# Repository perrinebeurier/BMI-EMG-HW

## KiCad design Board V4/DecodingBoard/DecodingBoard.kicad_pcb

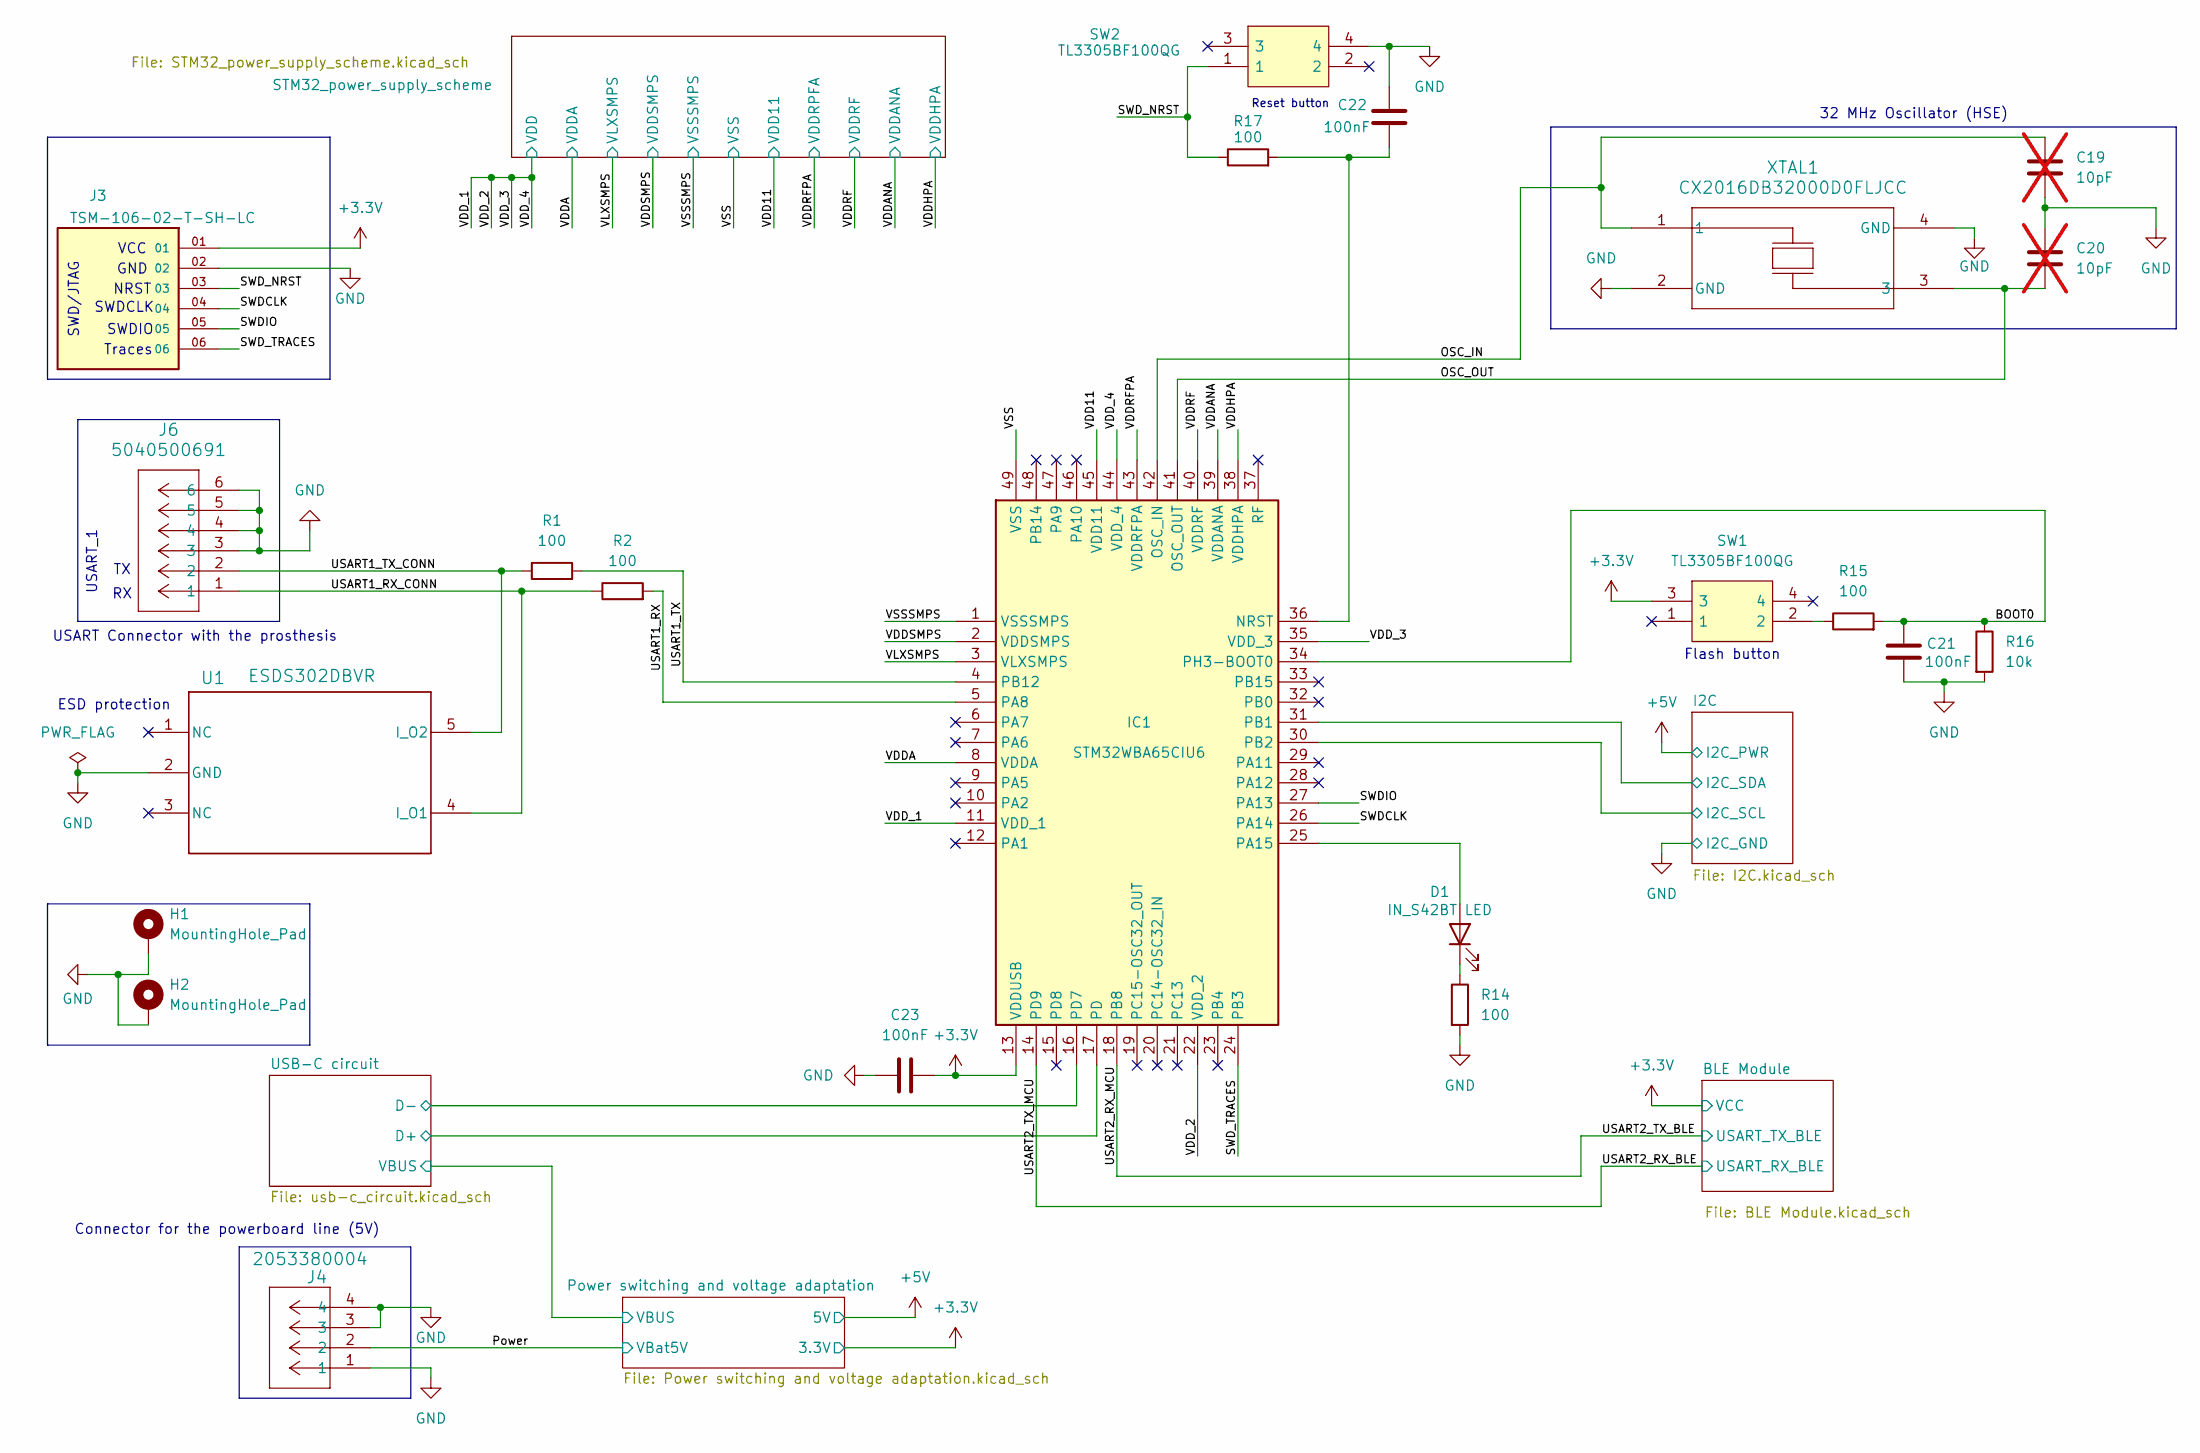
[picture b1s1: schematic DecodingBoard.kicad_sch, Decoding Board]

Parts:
C19, C20: 10pF; C_0603_1608Metric; not fitted
C21, C22, C23: 100nF; C_0402_1005Metric
D1: IN_S42BT LED; LED_0402_1005Metric
H1, H2: MountingHole_Pad; MountingHole_2.2mm_M2_DIN965_Pad
IC1: STM32WBA65CIU6; QFN50P700X700X60-49N-D; Manufacturer_Part_Number STM32WBA65CIU6; Mouser Part Number 511-STM32WBA65CIU6
J3: TSM-106-02-T-SH-LC; SAMTEC_TSM-106-02-T-SH-LC; PARTREV R
J4: 2053380004; CONN_2053380000-SD_02_MOL
J6: 5040500691; CONN_5040500491_MOL
R1, R2, R14, R15, R17: 100; R_0402_1005Metric
R16: 10k; R_0402_1005Metric
SW1, SW2: TL3305BF100QG; TL3305BF160QG; Mouser Part Number 612-TL3305BF100QG
U1: ESDS302DBVR; SOT95P280X145-5N; Mouser Part Number 595-ESDS302DBVR
XTAL1: CX2016DB32000D0FLJCC; Mouser Part Number 581-CX2016DB32DFLJCC

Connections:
+3.3V: C23.2, IC1.2 (VDDSMPS), IC1.8 (VDDA), IC1.11 (VDD_1), IC1.13 (VDDUSB), IC1.22 (VDD_2), IC1.35 (VDD_3), IC1.40 (VDDRF), IC1.44 (VDD_4), J3.01, SW1.3; also elsewhere on the board
/BOOT0: C21.1, IC1.34 (PH3-BOOT0), R15.2, R16.1
/I2C/I2C_SCL: IC1.30 (PB2); also elsewhere on the board
/I2C/I2C_SDA: IC1.31 (PB1); also elsewhere on the board
/OSC_IN: C19.1, IC1.42 (OSC_IN), XTAL1.1
/OSC_OUT: C20.2, IC1.41 (OSC_OUT), XTAL1.3
/Power: J4.2; also elsewhere on the board
/SWDCLK: IC1.26 (PA14), J3.04
/SWDIO: IC1.27 (PA13), J3.05
/SWD_NRST: J3.03, R17.1, SW2.1
/SWD_TRACES: IC1.24 (PB3), J3.06
/USART1_RX: IC1.5 (PA8), R2.2
/USART1_RX_CONN: J6.1, R2.1, U1.4 (I_O1)
/USART1_TX: IC1.4 (PB12), R1.2
/USART1_TX_CONN: J6.2, R1.1, U1.5 (I_O2)
/USART2_RX_BLE: IC1.14 (PD9); also elsewhere on the board
/USART2_RX_MCU: IC1.18 (PB8); also elsewhere on the board
/USB-C circuit/D+: IC1.17 (PD); also elsewhere on the board
/USB-C circuit/D-: IC1.16 (PD7); also elsewhere on the board
/VDD11: IC1.39 (VDDANA), IC1.43 (VDDRFPA), IC1.45 (VDD11); also elsewhere on the board
/VDDHPA: IC1.38 (VDDHPA); also elsewhere on the board
/VLXSMPS: IC1.3 (VLXSMPS); also elsewhere on the board
GND: C19.2, C20.1, C21.2, C22.2, C23.1, H1.1 (1_1), H2.1 (1_1), IC1.1 (VSSSMPS), IC1.49 (VSS), J3.02, J4.1, J4.3, J4.4, J6.3, J6.4, J6.5, J6.6, R14.2, R16.2, SW2.4, U1.2 (GND), XTAL1.2 (GND), XTAL1.4 (GND); also elsewhere on the board
unnamed: D1.2 (A), IC1.25 (PA15)
unnamed: D1.1 (K), R14.1
unnamed: C22.1, IC1.36 (NRST), R17.2
unnamed: R15.1, SW1.2

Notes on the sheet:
GND
SWDIO
Flash button
NRST
ESD protection
Traces
USART Connector with the prosthesis
USART_1
SWD/JTAG
Connector for the powerboard line (5V)
SWDCLK
VCC
Reset button
32 MHz Oscillator (HSE)

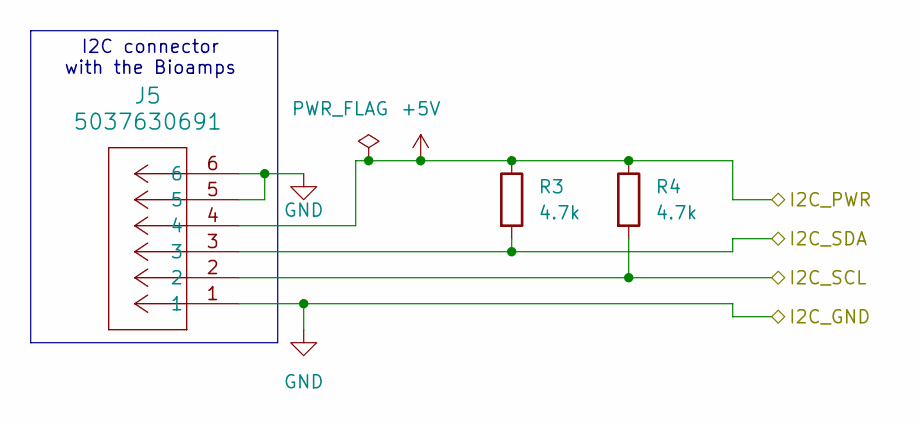
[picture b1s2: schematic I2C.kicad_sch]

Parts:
J5: 5037630691; CONN_5037630000-SD_04_MOL
R3, R4: 4.7k; R_0603_1608Metric

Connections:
+5V: J5.4, R3.1, R4.1; also elsewhere on the board
/I2C/I2C_SCL: J5.2, R4.2; also elsewhere on the board
/I2C/I2C_SDA: J5.3, R3.2; also elsewhere on the board
GND: J5.1, J5.5, J5.6; also elsewhere on the board

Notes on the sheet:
I2C connector with the Bioamps

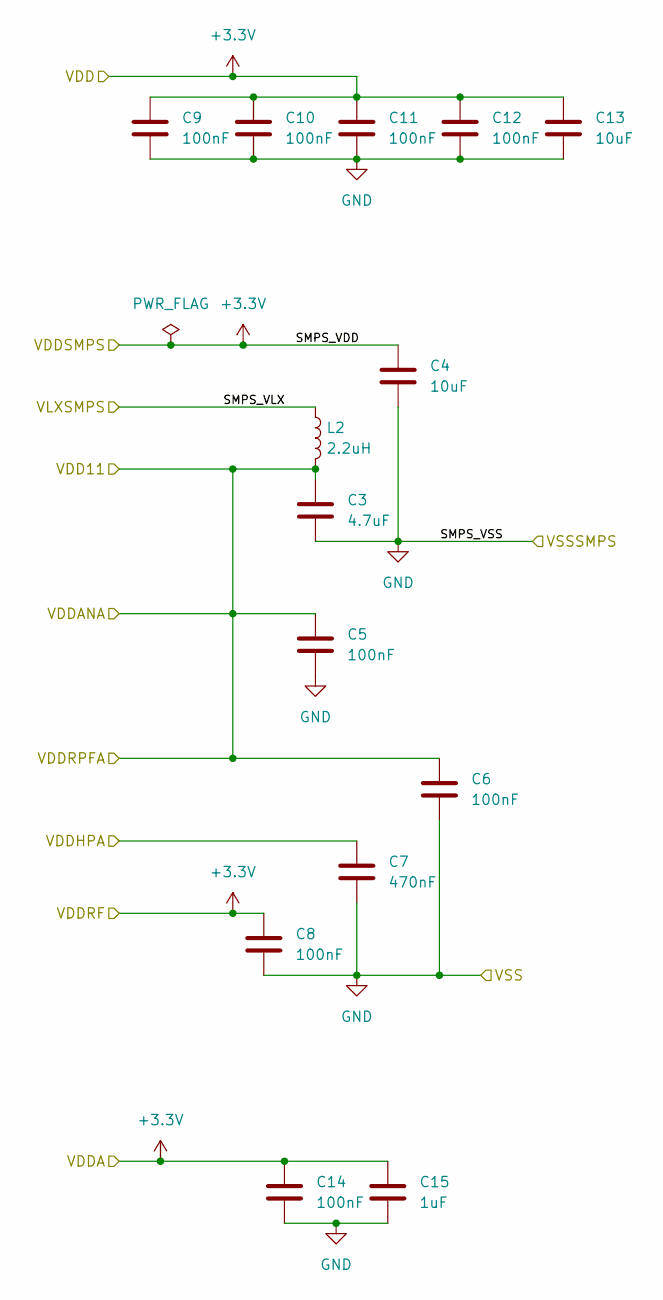
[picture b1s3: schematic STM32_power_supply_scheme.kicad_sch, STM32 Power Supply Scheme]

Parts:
C3: 4.7uF; C_0603_1608Metric
C4, C13: 10uF; C_0603_1608Metric
C5, C6, C8, C9, C10, C11, C12, C14: 100nF; C_0402_1005Metric
C7: 470nF; C_0402_1005Metric
C15: 1uF; C_0402_1005Metric
L2: 2.2uH; L_0805_2012Metric

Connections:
+3.3V: C4.1, C8.1, C9.1, C10.1, C11.1, C12.1, C13.1, C14.1, C15.1; also elsewhere on the board
/VDD11: C3.1, C5.1, C6.1, L2.2; also elsewhere on the board
/VDDHPA: C7.1; also elsewhere on the board
/VLXSMPS: L2.1; also elsewhere on the board
GND: C3.2, C4.2, C5.2, C6.2, C7.2, C8.2, C9.2, C10.2, C11.2, C12.2, C13.2, C14.2, C15.2; also elsewhere on the board

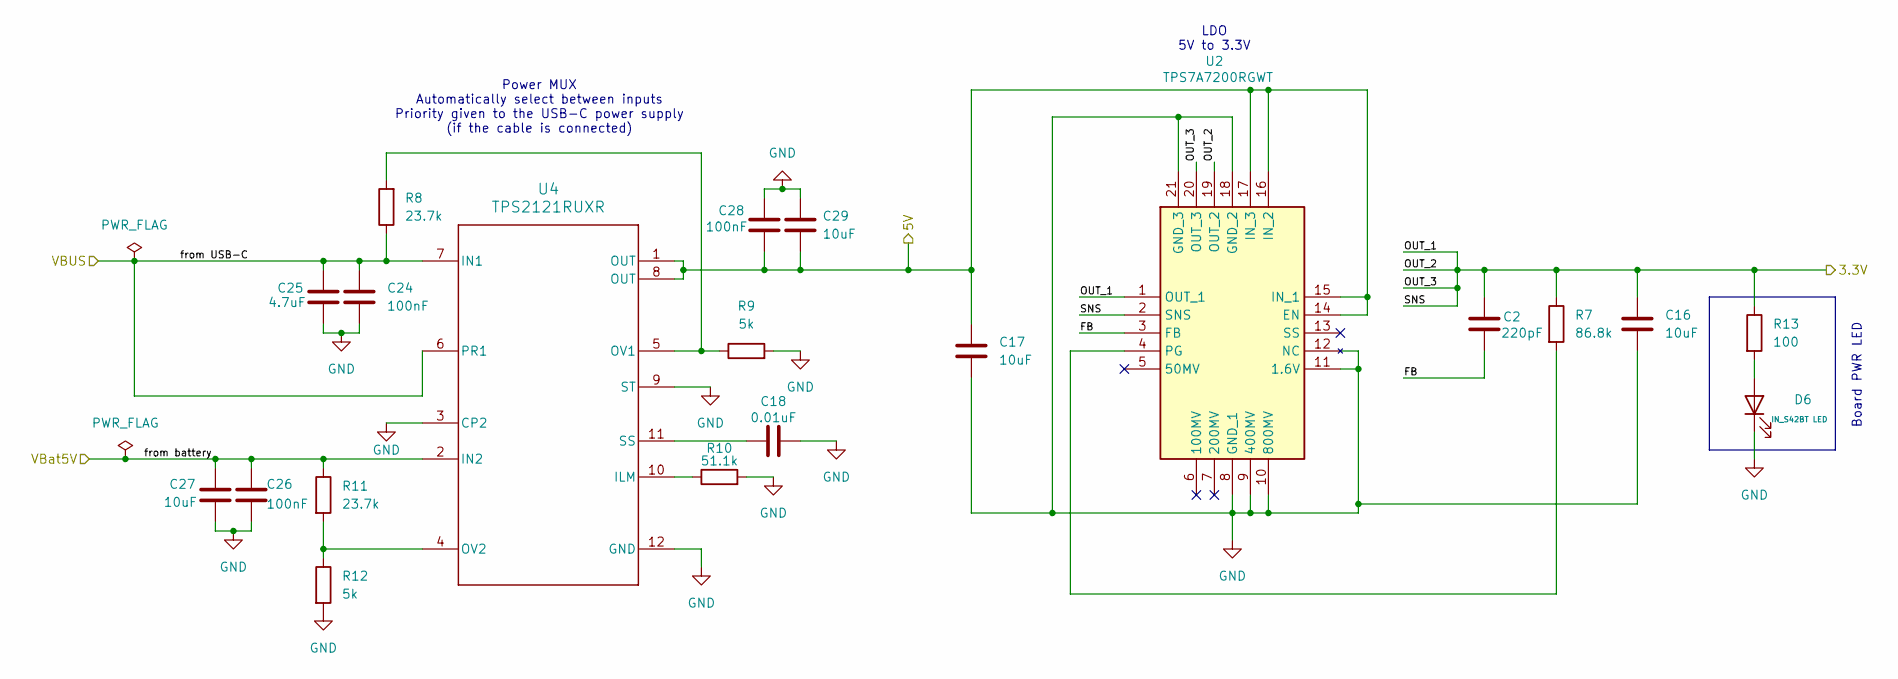
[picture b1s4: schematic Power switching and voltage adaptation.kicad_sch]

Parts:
C2: 220pF; C_0402_1005Metric
C16, C17, C27, C29: 10uF; C_0603_1608Metric
C18: 0.01uF; C_0402_1005Metric
C24, C26, C28: 100nF; C_0402_1005Metric
C25: 4.7uF; C_0603_1608Metric
D6: IN_S42BT LED; LED_0402_1005Metric
R7: 86.8k; R_0603_1608Metric
R8, R11: 23.7k; R_0402_1005Metric
R9, R12: 5k; R_0402_1005Metric
R10: 51.1k; R_0402_1005Metric
R13: 100; R_0402_1005Metric
U2: TPS7A7200RGWT; QFN65P500X500X100-21N-D; Manufacturer_Part_Number TPS7A7200RGWT; Mouser Part Number 595-TPS7A7200RGWT
U4: TPS2121RUXR; Mouser Part Number 595-TPS2121RUXR

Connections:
+3.3V: C2.1, C16.1, R7.1, R13.1, U2.1 (OUT_1), U2.2 (SNS), U2.19 (OUT_2), U2.20 (OUT_3); also elsewhere on the board
+5V: C17.1, C28.2, C29.2, U2.14 (EN), U2.15 (IN_1), U2.16 (IN_2), U2.17 (IN_3), U4.1 (OUT), U4.8 (OUT); also elsewhere on the board
/Power: C26.1, C27.1, R11.1, U4.2 (IN2); also elsewhere on the board
/Power switching and voltage adaptation/FB: C2.2, U2.3 (FB)
/Power switching and voltage adaptation/from USB-C: C24.1, C25.1, R8.1, U4.6 (PR1), U4.7 (IN1); also elsewhere on the board
GND: C16.2, C17.2, C18.2, C24.2, C25.2, C26.2, C27.2, C28.1, C29.1, D6.1 (K), R9.2, R10.2, R12.2, U2.8 (GND_1), U2.9 (400MV), U2.10 (800MV), U2.11 (1.6V), U2.12 (NC), U2.18 (GND_2), U2.21 (GND_3), U4.3 (CP2), U4.9 (ST), U4.12 (GND); also elsewhere on the board
unnamed: D6.2 (A), R13.2
unnamed: R7.2, U2.4 (PG)
unnamed: R10.1, U4.10 (ILM)
unnamed: R8.2, R9.1, U4.5 (OV1)
unnamed: R11.2, R12.1, U4.4 (OV2)
unnamed: C18.1, U4.11 (SS)

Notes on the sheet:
Power MUX Automatically select between inputs Priority given to the USB-C power supply (if the cable is connected)
LDO 5V to 3.3V
Board PWR LED

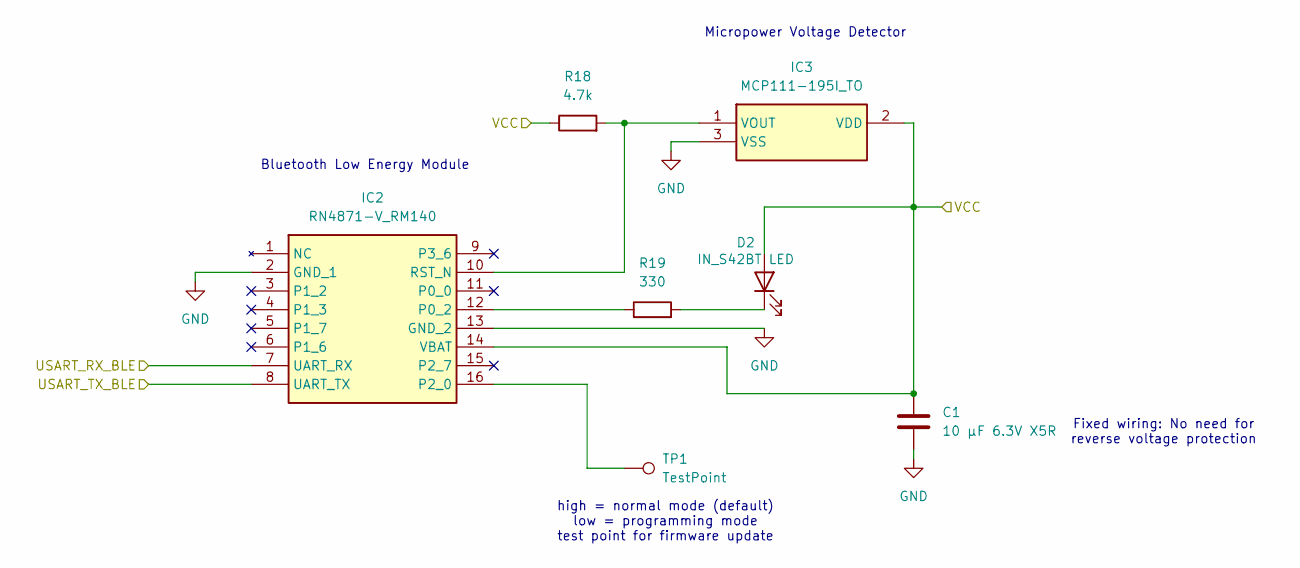
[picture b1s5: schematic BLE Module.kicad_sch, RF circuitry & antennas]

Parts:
C1: 10 μF 6.3V X5R; C_0805_2012Metric
D2: IN_S42BT LED; LED_0402_1005Metric
IC2: RN4871-V_RM140; RN4871VRM140; Manufacturer_Part_Number RN4871-V/RM140; Mouser Part Number 579-RN4871-V/RM140
IC3: MCP111-195I_TO; LR645N3GP013; Manufacturer_Part_Number MCP111-195I/TO; Mouser Part Number 579-MCP111-195I/TO
R18: 4.7k; R_0402_1005Metric
R19: 330; R_0402_1005Metric
TP1: TestPoint; TestPoint_Pad_D1.0mm

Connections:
+3.3V: C1.1, D2.2 (A), IC2.14 (VBAT), IC3.2 (VDD), R18.1; also elsewhere on the board
/USART2_RX_BLE: IC2.7 (UART_RX); also elsewhere on the board
/USART2_RX_MCU: IC2.8 (UART_TX); also elsewhere on the board
GND: C1.2, IC2.2 (GND_1), IC2.13 (GND_2), IC3.3 (VSS); also elsewhere on the board
unnamed: D2.1 (K), R19.2
unnamed: IC2.12 (P0_2), R19.1
unnamed: IC2.16 (P2_0), TP1.1 (1_1)
unnamed: IC2.10 (RST_N), IC3.1 (VOUT), R18.2

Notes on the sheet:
Bluetooth Low Energy Module
high = normal mode (default) low = programming mode test point for firmware update
Fixed wiring: No need for reverse voltage protection
Micropower Voltage Detector

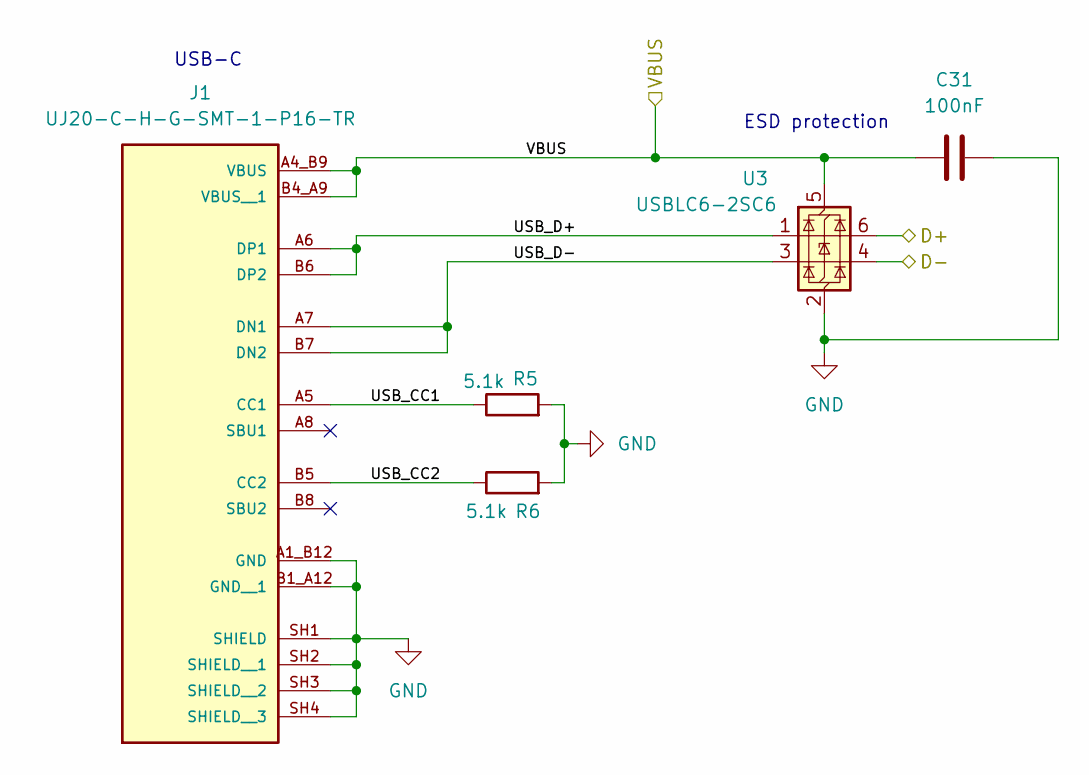
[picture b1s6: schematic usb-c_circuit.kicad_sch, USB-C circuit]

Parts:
C31: 100nF; C_0402_1005Metric
J1: UJ20-C-H-G-SMT-1-P16-TR; SAMESKY_UJ20-C-H-G-SMT-1-P16-TR; PARTREV 1.0; Mouser Part Number 179-UJ20CHGSMT1P16TR
R5, R6: 5.1k; R_0402_1005Metric
U3: USBLC6-2SC6; SOT-23-6; Mouser Part Number 511-USBLC6-2SC6

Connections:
/Power switching and voltage adaptation/from USB-C: C31.1, J1.A4_B9 (VBUS), J1.B4_A9 (VBUS__1), U3.5 (VBUS); also elsewhere on the board
/USB-C circuit/D+: U3.6 (I/O1); also elsewhere on the board
/USB-C circuit/D-: U3.4 (I/O2); also elsewhere on the board
/USB-C circuit/USB_CC1: J1.A5 (CC1), R5.1
/USB-C circuit/USB_CC2: J1.B5 (CC2), R6.1
/USB-C circuit/USB_D+: J1.A6 (DP1), J1.B6 (DP2), U3.1 (I/O1)
/USB-C circuit/USB_D-: J1.A7 (DN1), J1.B7 (DN2), U3.3 (I/O2)
GND: C31.2, J1.A1_B12 (GND), J1.B1_A12 (GND__1), J1.SH1 (SHIELD), J1.SH2 (SHIELD__1), J1.SH3 (SHIELD__2), J1.SH4 (SHIELD__3), R5.2, R6.2, U3.2 (GND); also elsewhere on the board

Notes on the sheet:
ESD protection
USB-C

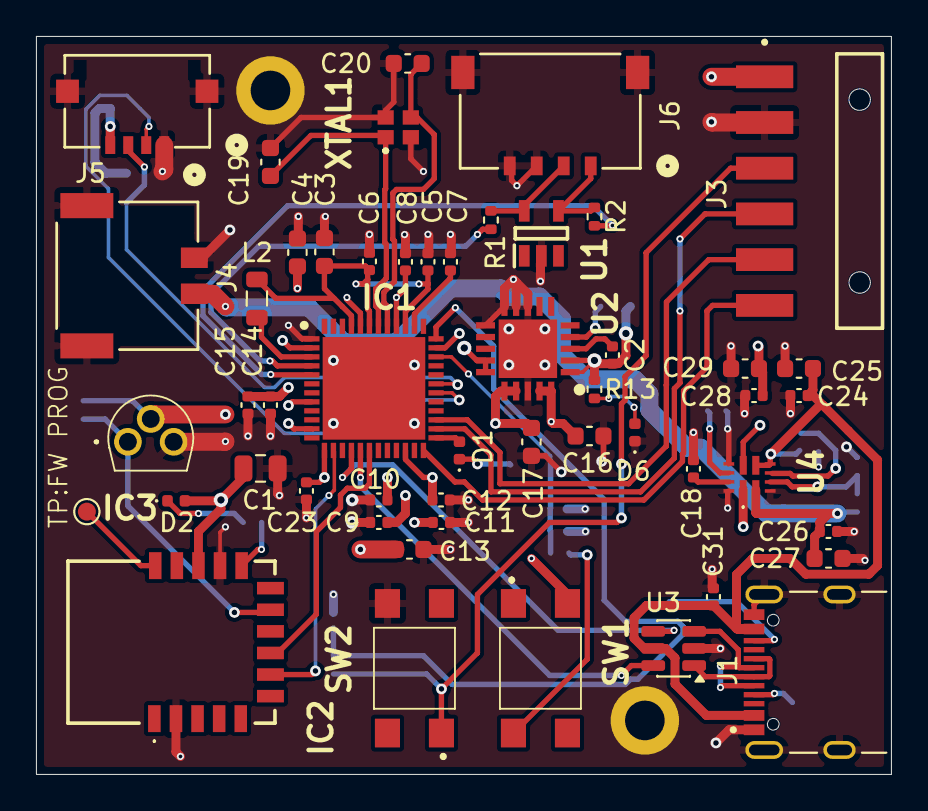
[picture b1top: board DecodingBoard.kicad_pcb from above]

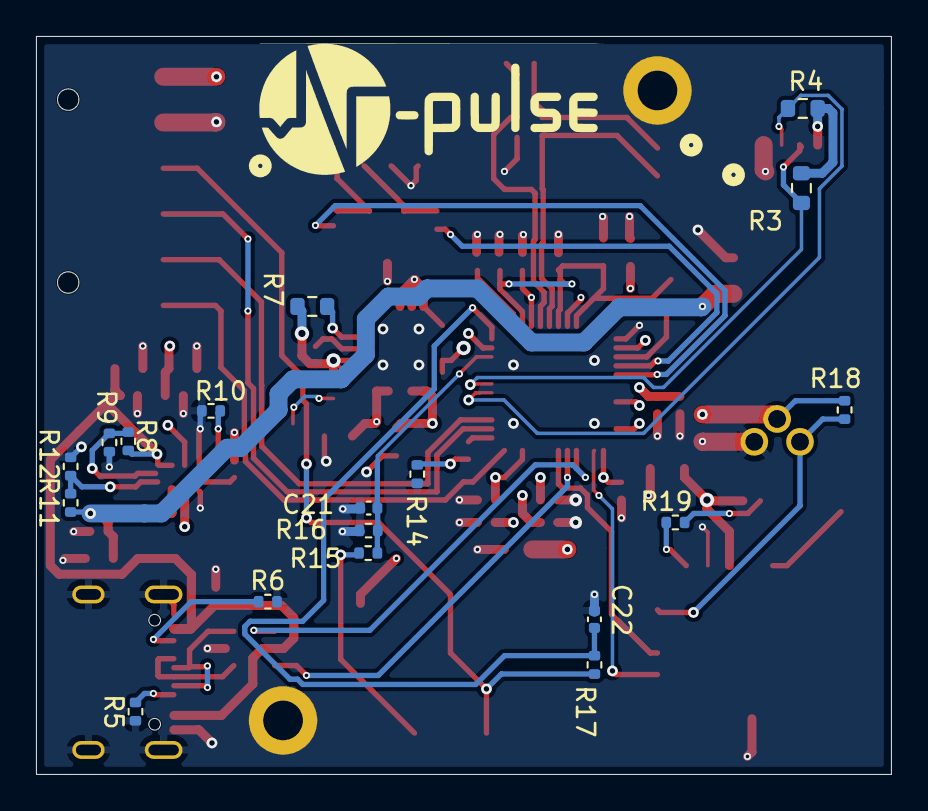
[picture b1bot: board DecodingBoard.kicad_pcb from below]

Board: 4 copper layers, 47.5 x 41.0 mm, 71 parts (18 on the bottom side), 44 nets.
